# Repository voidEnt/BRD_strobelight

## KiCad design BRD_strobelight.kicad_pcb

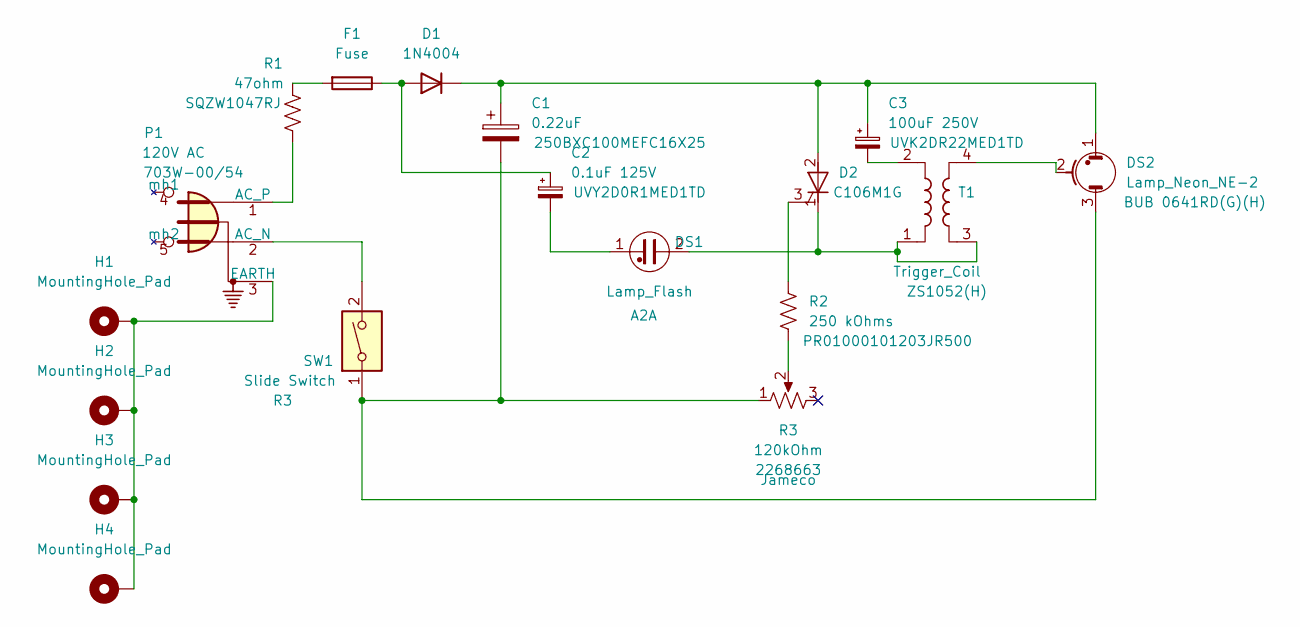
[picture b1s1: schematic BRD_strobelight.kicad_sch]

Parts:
C1: 0.22uF; CP_Radial_D16.0mm_P7.50mm; Part 250BXC100MEFC16X25
C2: 0.1uF 125V; CP_Radial_D6.3mm_P2.50mm; Part UVY2D0R1MED1TD
C3: 100uF 250V; CP_Radial_D6.3mm_P2.50mm; Part UVK2DR22MED1TD
D1: TIC106 alt (C106M1G); D_DO-34_SOD68_P12.70mm_Horizontal; Part 1N4004
D2: 1N4004; PinHeader_1x03_P2.54mm_Vertical; Part C106M1G
DS1: Lamp_Flash; SolderWire-0.1sqmm_1x02_P3.6mm_D0.4mm_OD1mm; Part A2A
DS2: Lamp_Neon_NE-2; SolderWire-0.75sqmm_1x03_P7mm_D1.25mm_OD3.5mm; Part BUB 0641RD(G)(H)
F1: Fuse; Fuse_Littelfuse_395Series
H1, H2, H3, H4: MountingHole_Pad; MountingHole_2.5mm_Pad_TopBottom
P1: 120V AC; 703W-00_54; Part 703W-00/54
R1: 47ohm; SQZW1047RJ; Part SQZW1047RJ
R2: 250 kOhms; R_Axial_DIN0207_L6.3mm_D2.5mm_P15.24mm_Horizontal; Part PR01000101203JR500
R3: 120kOhm; SolderWire-0.75sqmm_1x02_P7mm_D1.25mm_OD3.5mm_Relief; Part 2268663
SW1: Slide Switch; SolderWire-0.75sqmm_1x02_P7mm_D1.25mm_OD3.5mm_Relief; Part R3
T1: Trigger_Coil; ZS1052(H); Part ZS1052(H)

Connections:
unnamed: C1.1, C3.1, D1.1 (K), D2.2 (A), DS2.1
unnamed: C1.2, DS2.3, R3.1, SW1.1
unnamed: C2.1, D1.2 (A), F1.1
unnamed: D2.1 (K), DS1.2, T1.1, T1.3
unnamed: D2.3 (G), R2.1
unnamed: C2.2, DS1.1
unnamed: DS2.2, T1.4
unnamed: F1.2, R1.1
unnamed: H1.1, H2.1, H3.1, H4.1, P1.3 (EARTH)
unnamed: P1.1 (AC_P), R1.2
unnamed: P1.2 (AC_N), SW1.2
unnamed: R2.2, R3.2
unnamed: C3.2, T1.2

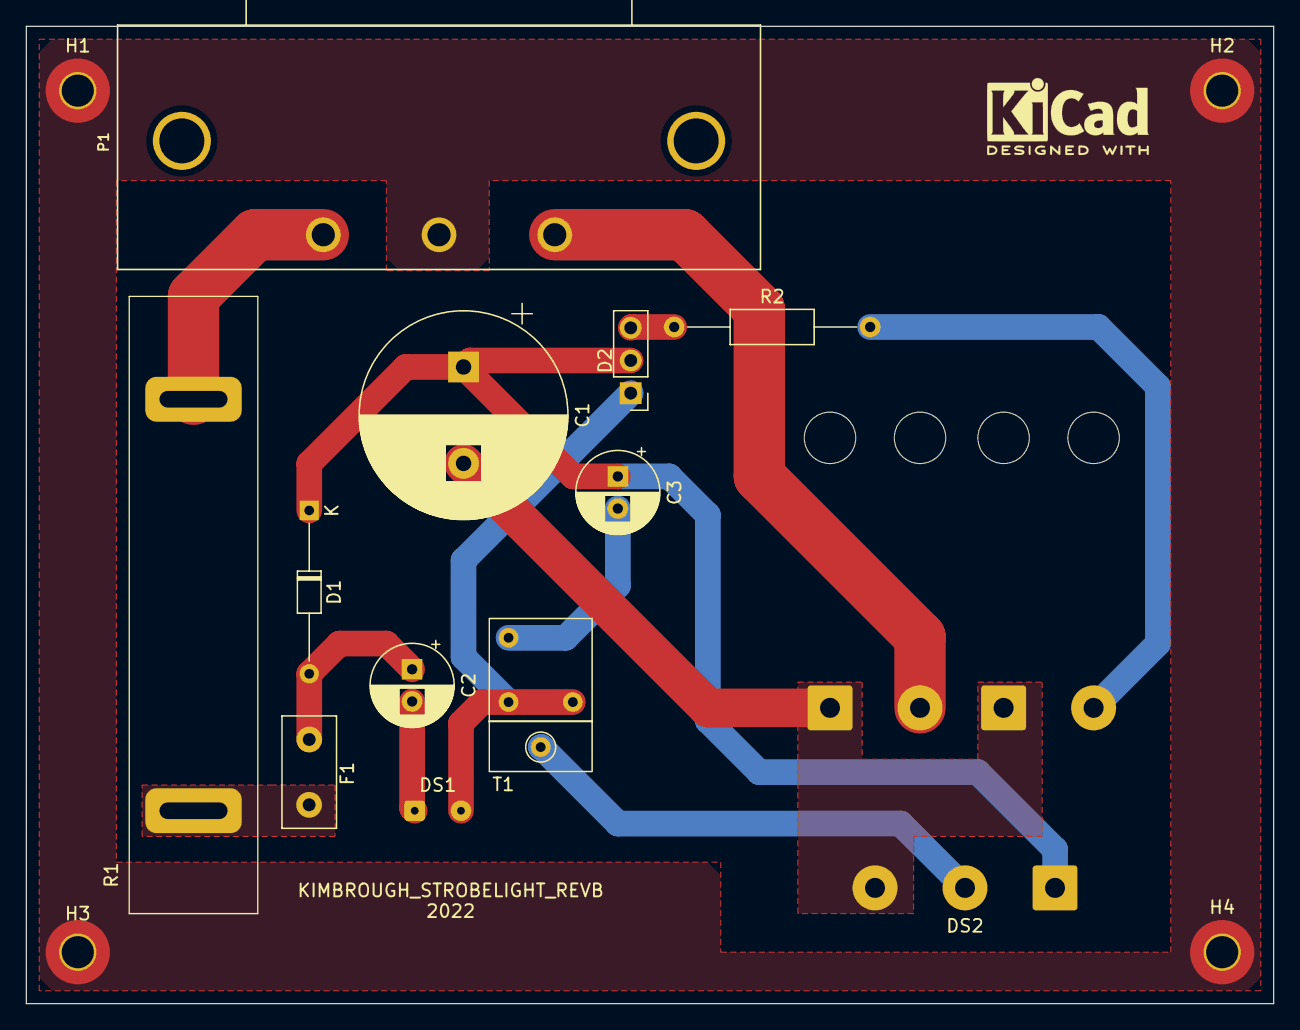
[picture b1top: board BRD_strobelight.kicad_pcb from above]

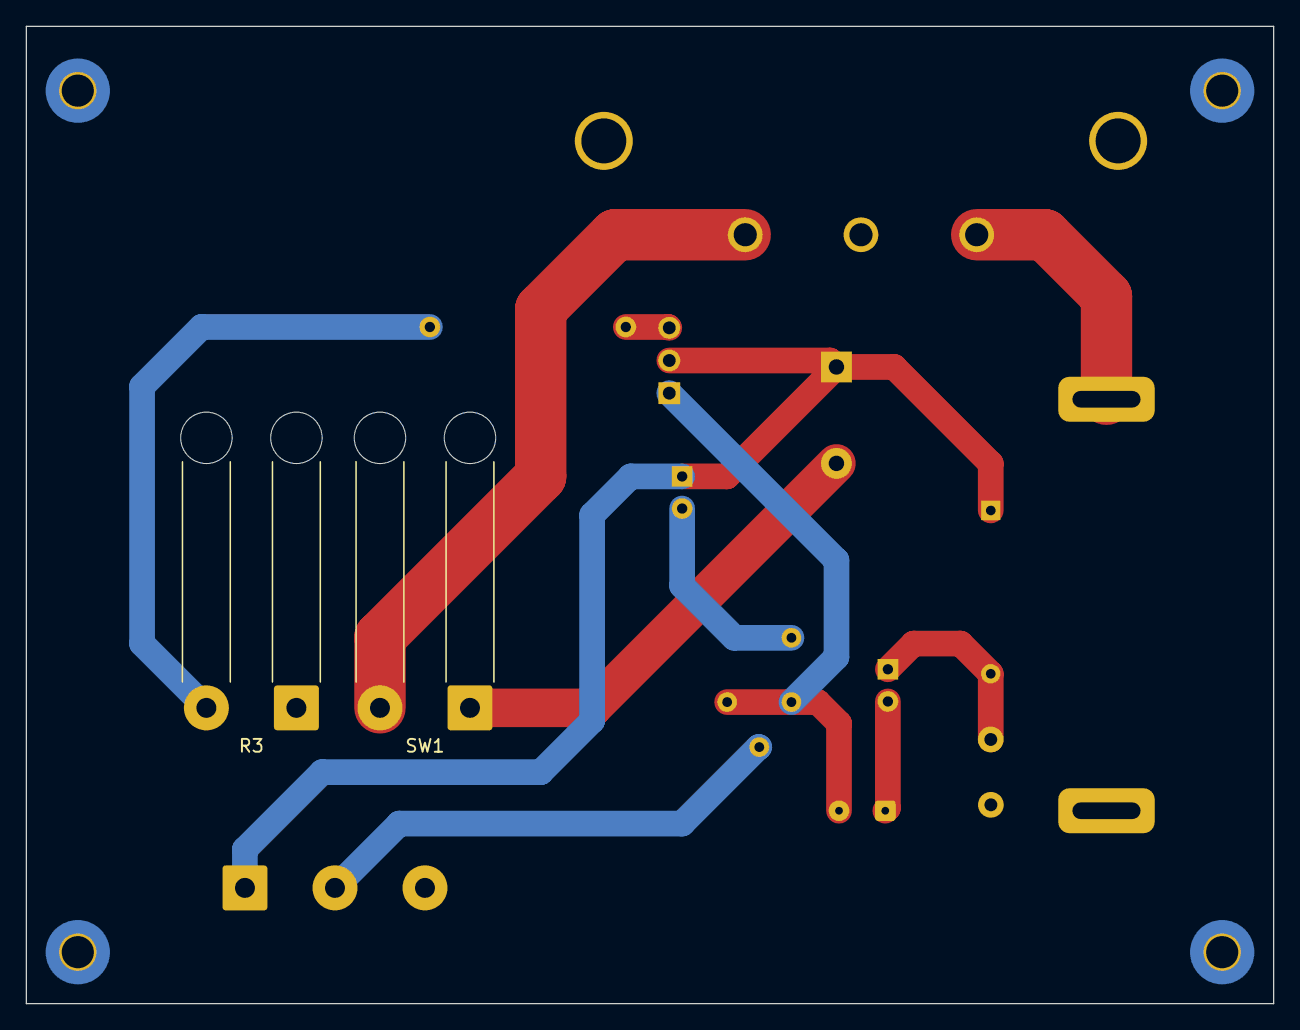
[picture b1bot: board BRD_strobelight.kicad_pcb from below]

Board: 2 copper layers, 97.0 x 76.0 mm, 18 parts (2 on the bottom side), 13 nets.
